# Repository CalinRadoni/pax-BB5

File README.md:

# PAx BaseBoard STM32L051K8T

The hardware board is the one created by me in 2017, published in [PAx5](https://github.com/CalinRadoni/PAx5) repository. The new addition is PlatformIO compatibility files to allow programming the board with 
Arduino, CMSIS, LibOpenCM3 or STM32Cube frameworks.

See the [docs site](https://calinradoni.github.io/pax-BB5/) for pinout, schematic and more.

## The code

In the `src` directory I have created blink test code for Arduino, CMSIS, LibOpenCM3 and STM32Cube.
The selection between directories is made through `platformio.ini` configuration file.

## Hardware details

- STM32L051K8T MCU
- RFM69HW transceiver module 868MHz
- M25P10 128kB Flash memory
- on-board LED
- on-board switch port

## Development Environment

- [PlatformIO](https://platformio.org) Core, version 5.1.1.
- editing was done in [Visual Studio Code](https://code.visualstudio.com)
- version control with [Git](https://git-scm.com)
- [KiCad EDA](http://kicad.org/) for hardware schematic and PCB board
- [GIMP](https://www.gimp.org/) and [Inkscape](https://inkscape.org/en/) for images

## License

*Unless otherwise specified:*

The software and documentation are released under the [GNU GPLv3](http://www.gnu.org/licenses/gpl-3.0.html) License. See the __LICENSE-GPLv3.txt__ file.

The hardware schematics are licensed under a [Creative Commons Attribution-ShareAlike 4.0 International License](http://creativecommons.org/licenses/by-sa/4.0/).
See the __LICENSE-CC-BY-SA-4.0.txt__ file.

The code for Arduino Variant is:

- Copyright (c) 2021, STMicroelectronics
- Copyright (c) 2021, CalinRadoni (https://github.com/CalinRadoni)

and released under the [BSD 3-Clause license](https://opensource.org/licenses/BSD-3-Clause).

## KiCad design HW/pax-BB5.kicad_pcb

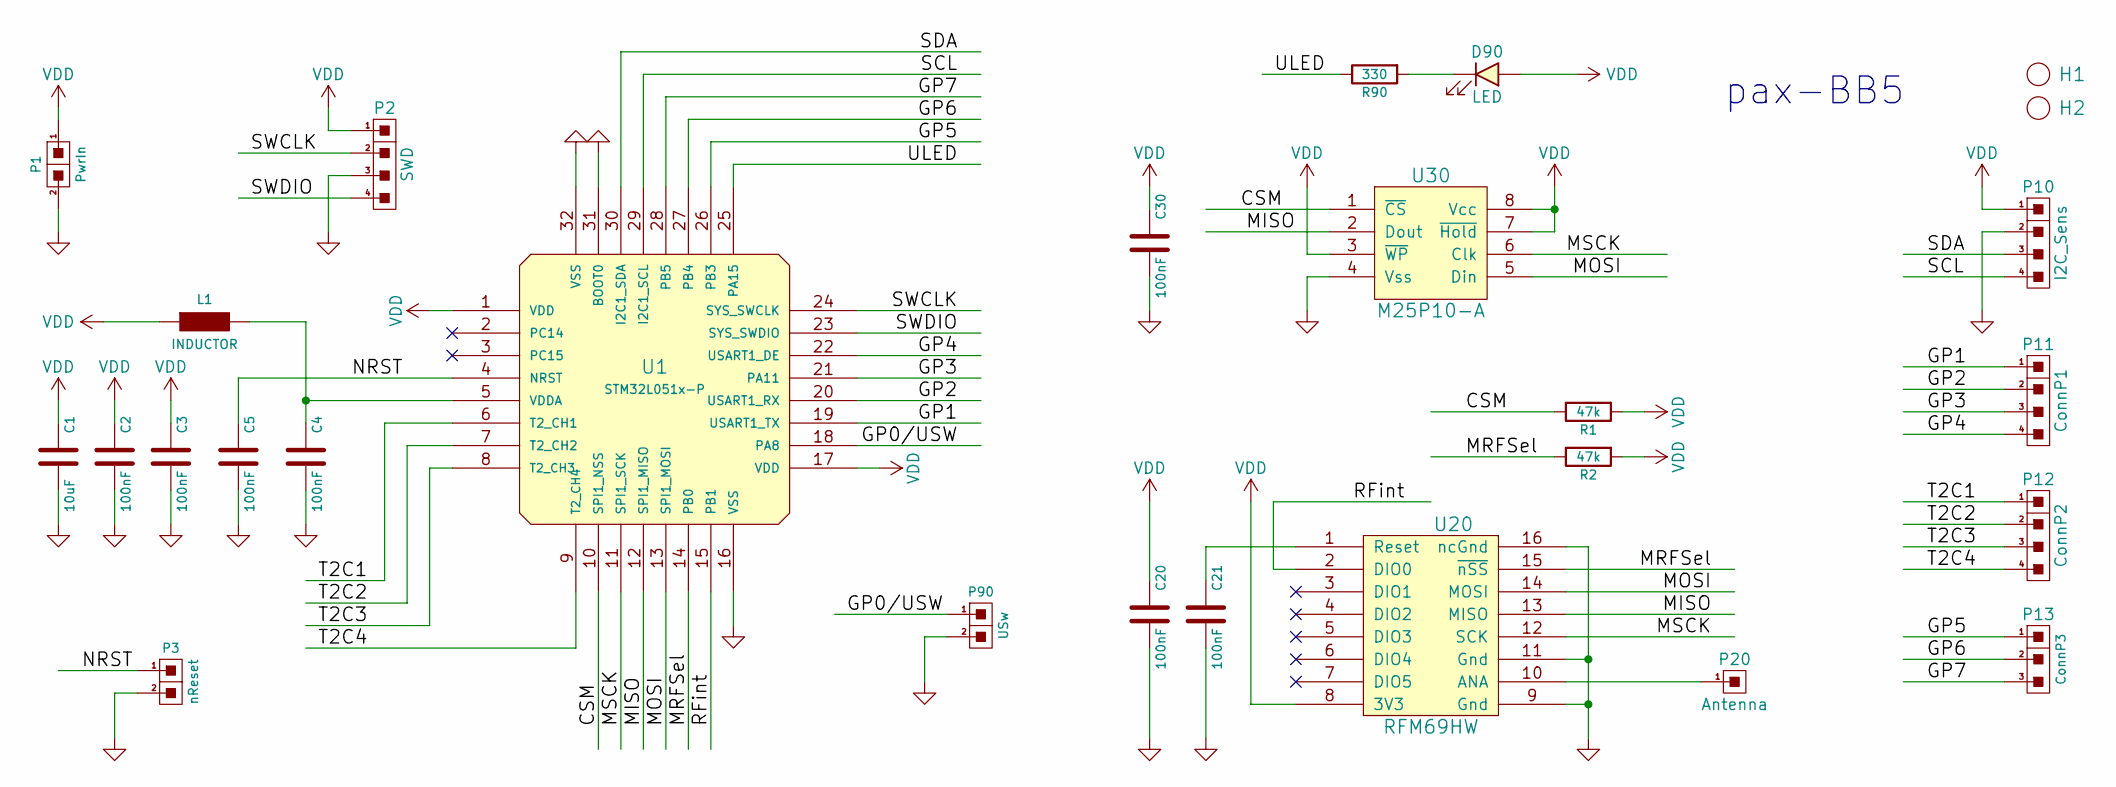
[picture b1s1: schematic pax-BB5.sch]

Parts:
C1: 10uF; C_1206_HandSoldering
C2, C3, C4, C5, C20, C21, C30: 100nF; C_0805_HandSoldering
D90: LED; LED_1206_HandSoldering
H1, H2: Hole; cHole
L1: INDUCTOR; R_1206_HandSoldering
P1: PwrIn; Pin_Header_Straight_1x02
P2: SWD; Pin_Header_Straight_1x04
P3: nReset; Pin_Header_Straight_1x02
P10: I2C_Sens; Pin_Header_Straight_1x04
P11: ConnP1; Pin_Header_Straight_1x04
P12: ConnP2; Pin_Header_Straight_1x04
P13: ConnP3; Pin_Header_Straight_1x03
P20: Antenna; Pin_Header_Straight_1x01
P90: USw; Pin_Header_Straight_1x02
R1, R2: 47k; R_0805_HandSoldering
R90: 330; R_1206_HandSoldering
U1: STM32L051x-P; cLQFP32-7
U20: RFM69HW
U30: M25P10-A; SOIC-8-N

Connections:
/CSM: R1.2, U1.10 (SPI1_NSS), U30.1 (~CS)
/GP0/USW: P90.1, U1.18 (PA8)
/GP1: P11.1, U1.19 (USART1_TX)
/GP2: P11.2, U1.20 (USART1_RX)
/GP3: P11.3, U1.21 (PA11)
/GP4: P11.4, U1.22 (USART1_DE)
/GP5: P13.1, U1.26 (PB3)
/GP6: P13.2, U1.27 (PB4)
/GP7: P13.3, U1.28 (PB5)
/MISO: U1.12 (SPI1_MISO), U20.13 (MISO), U30.2 (Dout)
/MOSI: U1.13 (SPI1_MOSI), U20.14 (MOSI), U30.5 (Din)
/MRFSel: R2.2, U1.14 (PB0), U20.15 (~nSS)
/MSCK: U1.11 (SPI1_SCK), U20.12 (SCK), U30.6 (Clk)
/NRST: C5.1, P3.1, U1.4 (NRST)
/RFint: U1.15 (PB1), U20.2 (DIO0)
/SCL: P10.4, U1.29 (I2C1_SCL)
/SDA: P10.3, U1.30 (I2C1_SDA)
/SWCLK: P2.2, U1.24 (SYS_SWCLK)
/SWDIO: P2.4, U1.23 (SYS_SWDIO)
/T2C1: P12.1, U1.6 (T2_CH1)
/T2C2: P12.2, U1.7 (T2_CH2)
/T2C3: P12.3, U1.8 (T2_CH3)
/T2C4: P12.4, U1.9 (T2_CH4)
/ULED: R90.2, U1.25 (PA15)
GND: C1.2, C2.2, C3.2, C4.2, C5.2, C20.2, C21.2, C30.2, P1.2, P2.3, P3.2, P10.2, P90.2, U1.16 (VSS), U1.31 (BOOT0), U1.32 (VSS), U20.9 (Gnd), U20.11 (Gnd), U20.16 (ncGnd), U30.4 (Vss)
unnamed: C4.1, L1.2, U1.5 (VDDA)
unnamed: C21.1, U20.1 (Reset)
unnamed: D90.K, R90.1
unnamed: P20.1, U20.10 (ANA)
VDD: C1.1, C2.1, C3.1, C20.1, C30.1, D90.A, L1.1, P1.1, P2.1, P10.1, R1.1, R2.1, U1.1 (VDD), U1.17 (VDD), U20.8 (3V3), U30.3 (~WP), U30.7 (~Hold), U30.8 (Vcc)

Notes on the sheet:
pax-BB5

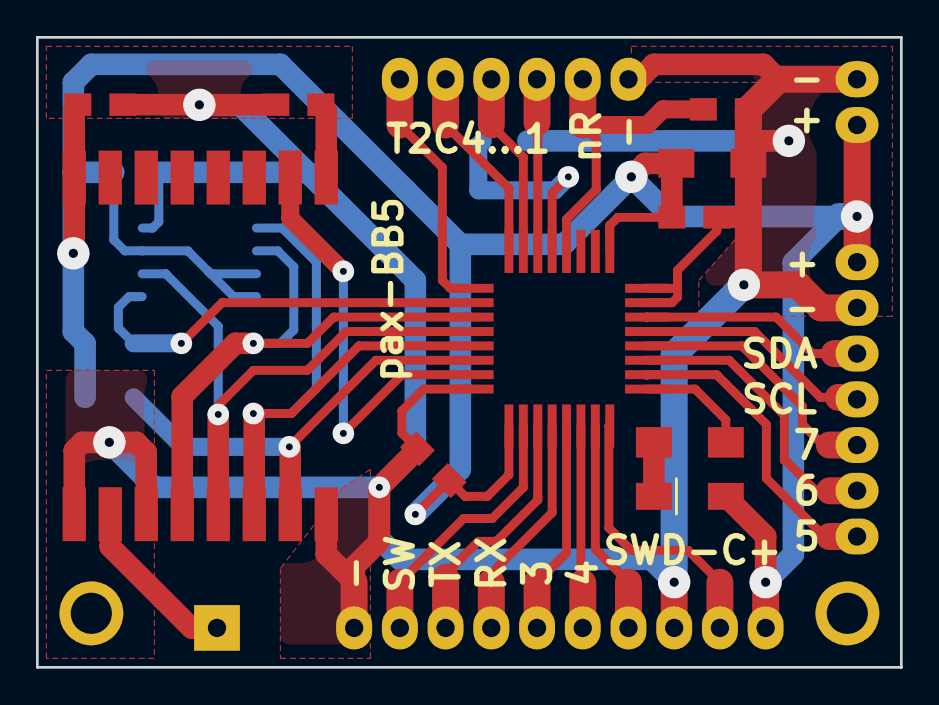
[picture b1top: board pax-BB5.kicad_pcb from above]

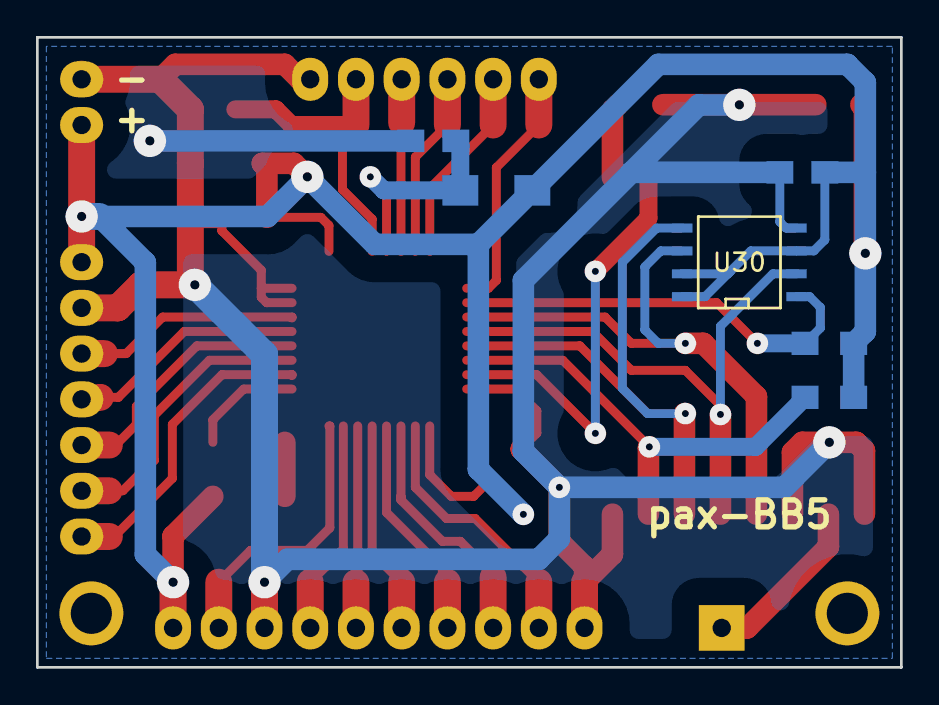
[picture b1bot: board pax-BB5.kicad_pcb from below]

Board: 2 copper layers, 48.0 x 35.0 mm, 27 parts (13 on the bottom side), 30 nets.

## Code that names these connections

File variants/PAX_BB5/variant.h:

/*
 *******************************************************************************
 * Copyright (c) 2021, STMicroelectronics
 * All rights reserved.
 *
 * This software component is licensed by ST under BSD 3-Clause license,
 * the "License"; You may not use this file except in compliance with the
 * License. You may obtain a copy of the License at:
 *                        opensource.org/licenses/BSD-3-Clause
 *
 *******************************************************************************
 *
 * Copyright (c) 2021, CalinRadoni (https://github.com/CalinRadoni)
 * 
 * This file is part of PAX_BB5 Arduino Variant (https://github.com/CalinRadoni/pax-BB5)
 * Original file was heavily modified for pax-BB5 board (STM32L051K8T MCU)
 *
 *******************************************************************************
 */

#ifndef _VARIANT_ARDUINO_STM32_
#define _VARIANT_ARDUINO_STM32_

#ifdef __cplusplus
extern "C" {
#endif // __cplusplus

/**
 * @brief Returns the exit code generated by calling SystemClock_Config
 *
 * The SystemClock_Config function will set an exit code with the bits as follow:
 * - bit 0 set = function was called
 * - bit 1 set = HAL_RCC_OscConfig execution error
 * - bit 2 set = HAL_RCC_ClockConfig execution error
 * - bit 3 set = HAL_RCCEx_PeriphCLKConfig execution error
 */
unsigned char SystemClock_Config_ExitCode(void);

/*----------------------------------------------------------------------------
 * STM32 pins
 *----------------------------------------------------------------------------*/

#define PA8   0  // User switch
#define PA9   1  // USART1 Tx
#define PA10  2  // USART1 Rx
#define PA11  3
#define PA12  4
#define PB3   5
#define PB4   6
#define PB5   7
#define PB6   8  // SCL
#define PB7   9  // SDA
#define PA0   A0 // ADC_IN0, T2C1
#define PA1   A1 // ADC_IN1, T2C2
#define PA2   A2 // ADC_IN2, T2C3
#define PA3   A3 // ADC_IN3, T2C4
#define PA15  14 // User LED
#define PB1   15 // IntRadio
#define PB0   16 // CSRadio
#define PA4   17 // CSMemory
#define PA5   18 // SPI1_SCK
#define PA6   19 // SPI1_MISO
#define PA7   20 // SPI1_MOSI
#define PA13  21 // SWDIO
#define PA14  22 // SWCLK
// PC14 not connected
// PC15 not connected

#define NUM_DIGITAL_PINS        23
#define NUM_ANALOG_INPUTS       4

// On-board LED pin number
#define LED_BUILTIN             PA15

// On-board user button
#define USER_BTN                PA8

// SPI definitions
#define PIN_SPI_SS_Mem          PA4
#define PIN_SPI_SS_Radio        PB0
#define PIN_SPI_SCK             PA5
#define PIN_SPI_MISO            PA6
#define PIN_SPI_MOSI            PA7
#define PIN_SPI_SS              PA4
#define PIN_SPI_SS1             PB0

// I2C definitions
#define PIN_WIRE_SDA            PB7
#define PIN_WIRE_SCL            PB6

// UART Definitions
#define SERIAL_UART_INSTANCE    1
// Default pin used for generic 'Serial' instance, mandatory for Firmata
#define PIN_SERIAL_RX           PA10
#define PIN_SERIAL_TX           PA9

// Timer Definitions
// Use TIM6/TIM7 when possible as servo and tone don't need GPIO output pin
#define TIMER_TONE              TIM6
#define TIMER_SERVO             TIM21

#ifdef __cplusplus
}
#endif

/*----------------------------------------------------------------------------
 * Arduino objects - C++ only
 *----------------------------------------------------------------------------*/

#ifdef __cplusplus
  // These serial port names are intended to allow libraries and architecture-neutral
  // sketches to automatically default to the correct port name for a particular type
  // of use.  For example, a GPS module would normally connect to SERIAL_PORT_HARDWARE_OPEN,
  // the first hardware serial port whose RX/TX pins are not dedicated to another use.
  //
  // SERIAL_PORT_MONITOR        Port which normally prints to the Arduino Serial Monitor
  //
  // SERIAL_PORT_USBVIRTUAL     Port which is USB virtual serial
  //
  // SERIAL_PORT_LINUXBRIDGE    Port which connects to a Linux system via Bridge library
  //
  // SERIAL_PORT_HARDWARE       Hardware serial port, physical RX & TX pins.
  //
  // SERIAL_PORT_HARDWARE_OPEN  Hardware serial ports which are open for use.  Their RX & TX
  //                            pins are NOT connected to anything by default.
  #define SERIAL_PORT_MONITOR       Serial
  #define SERIAL_PORT_HARDWARE      Serial
  #define SERIAL_PORT_HARDWARE_OPEN Serial
#endif

#endif /* _VARIANT_ARDUINO_STM32_ */

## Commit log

2021-04-04 Repository initialization
2021-04-04 Adds auxiliary files
2021-04-04 Adds the board and variant files for this board
2021-04-04 Adds platformio.ini for multiple frameworks
2021-04-04 Removes an incomplete and wrong README.md
2021-04-04 Adds README.md and license files
2021-04-04 Adds source files for build tests
2021-04-04 Adds documentation site
2021-04-04 Updates README
2021-04-05 Adds the updated KiCad project
2021-04-05 Updates the license
2021-04-05 Updates the schematic image
2021-11-08 Update README.md
    https://forum.kicad.info/t/warning-avoid-all-links-to-kicad-pcb-org-use-kicad-org/31521
2022-02-09 Rename some variant files for compatibility with ST STM32 (15.2.0) with framework-arduinoststm32 4.20100.211028 (2.1.0)
2022-02-09 Add useful 'define' and information about timers
